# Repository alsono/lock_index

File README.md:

# overview
- this is a pcb with muliple blinking leds that use a 555 timer to cycle between them
- i have never used one of the said timers before so this was fun to learn
- shoutout to yes for explaining these to me
- shoutout to stasis for the guide used for this
- this is supposed to be the index lock which i will work on decorating hopefully
# the schematic

# the pcb design

# the 555 blinker led pcb render

.png)

## components needed to make
### included in the blinky board kit from stasis which is technically 10$
- 10 leds (literal cents from any hardware store) 1$
- a 555 timer used for blinking the leds themselves 0.70$
- a cd4017be same used in this link https://www.digikey.com/en/products/detail/texas-instruments/CD4017BE/67253?msockid=1e2431194f71648f270924934eac65ac (used for wiring a lot of leds in this case all 10) costs $1.39 (this might be harder to find but it should be pretty common in specialized electrical engineering stores)
- a 50k ohm potentiometer 0.35$
- a 470 ohm resistor 0.03$
- a 1k resistor 0.02$
- a 0.01 uF capacitor 0.45$
- a 1 uF polarized capacitor 0.20$
### NOT included in said kit
- the pcb itself get it from jlcpcb by loading gbr.zip in there the board should be 2-4$ depending on regional pricing
  # total bill
### 8.44$ minus shipping and tax
### you will also need a soldering iron and solder, just don't get burnt!!

## sidenotes
i will adding an image of the decorated final version here

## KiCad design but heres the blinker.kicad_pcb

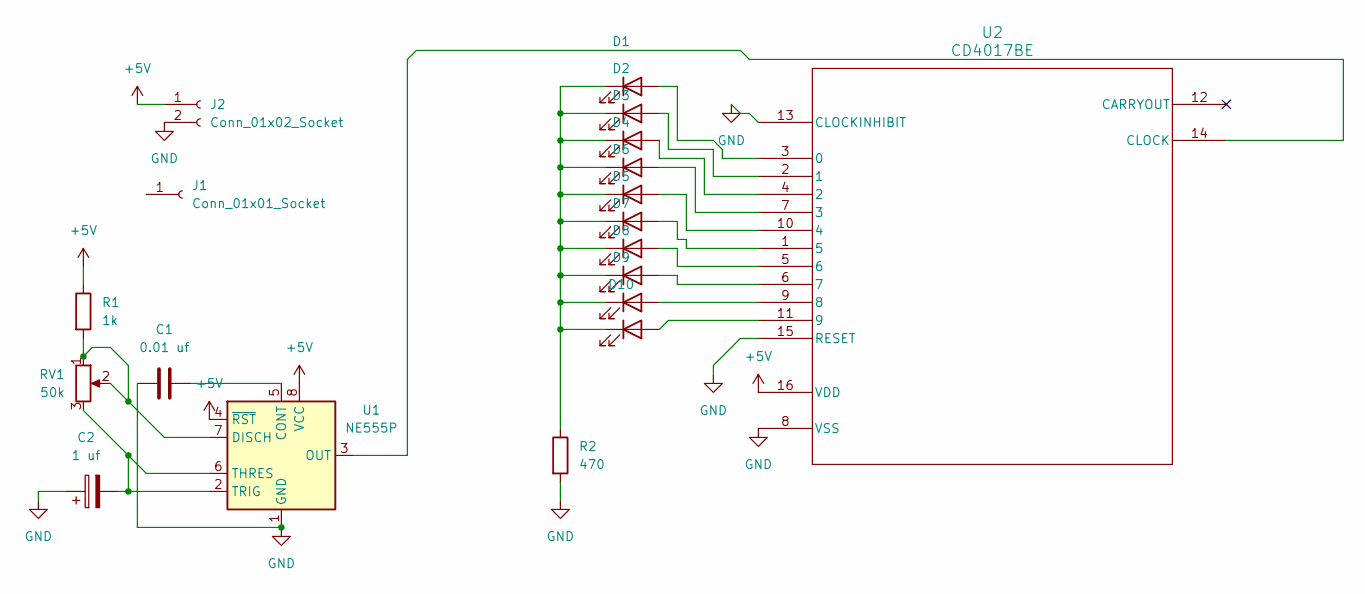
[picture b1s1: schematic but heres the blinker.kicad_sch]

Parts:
C1: 0.01 uf; C_Disc_D7.5mm_W2.5mm_P5.00mm
C2: 1 uf; CP_Radial_D5.0mm_P2.00mm
D1, D2, D3, D4, D5, D6, D7, D8, D9, D10: LED; LED_D3.0mm
J1: Conn_01x01_Socket; PinHeader_1x01_P2.54mm_Vertical
J2: Conn_01x02_Socket; PinHeader_1x02_P2.54mm_Vertical
R1: 1k; R_Axial_DIN0207_L6.3mm_D2.5mm_P7.62mm_Horizontal
R2: 470; R_Axial_DIN0207_L6.3mm_D2.5mm_P7.62mm_Horizontal
RV1: 50k; Potentiometer_Vishay_T93YA_Vertical
U1: NE555P; DIP-8_W7.62mm
U2: CD4017BE; N16

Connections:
+5V: J2.1, R1.1, U1.4 (~RST), U1.8 (VCC), U2.16 (VDD)
GND: C1.1, C2.1, J2.2, R2.2, U1.1 (GND), U2.8 (VSS), U2.13 (CLOCKINHIBIT), U2.15 (RESET)
unnamed: D1.2 (A), U2.3 (0)
unnamed: D1.1 (K), D2.1 (K), D3.1 (K), D4.1 (K), D5.1 (K), D6.1 (K), D7.1 (K), D8.1 (K), D9.1 (K), D10.1 (K), R2.1
unnamed: D2.2 (A), U2.2 (1)
unnamed: D3.2 (A), U2.4 (2)
unnamed: D4.2 (A), U2.7 (3)
unnamed: D5.2 (A), U2.1 (5)
unnamed: D6.2 (A), U2.10 (4)
unnamed: D7.2 (A), U2.5 (6)
unnamed: D8.2 (A), U2.6 (7)
unnamed: D9.2 (A), U2.9 (8)
unnamed: D10.2 (A), U2.11 (9)
unnamed: C1.2, U1.5 (CONT)
unnamed: R1.2, RV1.1, RV1.2, U1.7 (DISCH)
unnamed: U1.3 (OUT), U2.14 (CLOCK)
unnamed: C2.2, RV1.3, U1.2 (TRIG), U1.6 (THRES)

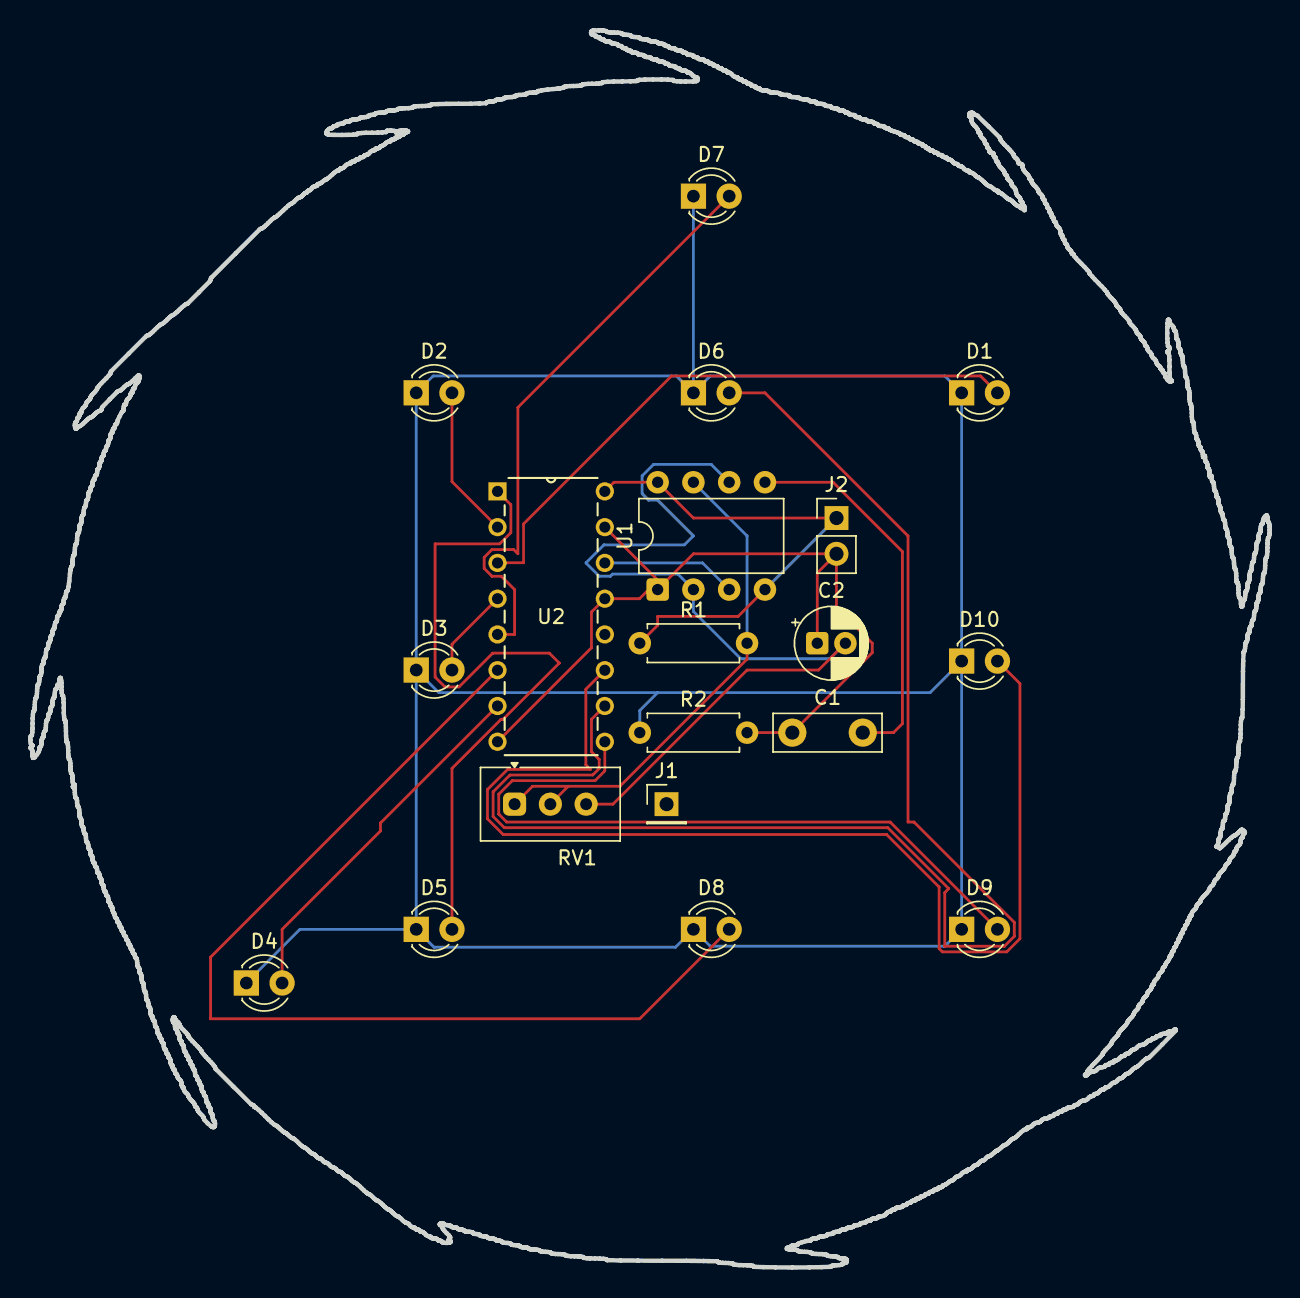
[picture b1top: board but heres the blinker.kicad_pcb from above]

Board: 2 copper layers, 88.0 x 87.8 mm, 19 parts (0 on the bottom side), 17 nets.

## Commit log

2026-06-23 what you'll be buying
